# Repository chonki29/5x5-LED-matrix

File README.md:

# DIY 5x5 LED Matrix Digital Dice

A DIY 5x5 LED matrix made with 25 LEDs, an ESP32 and a zero PCB.

The matrix can display numbers 1–6 and works as a simple digital dice. Pressing the button generates a random number and shows a short rolling animation before displaying the result.

## Hardware

- ESP32
- 25 LEDs
- 5 × 330Ω resistors
- Push button
- Zero PCB

## Pinout

Rows:

- R1 → GPIO 22
- R2 → GPIO 19
- R3 → GPIO 23
- R4 → GPIO 18
- R5 → GPIO 5

Columns:

- C1 → GPIO 27
- C2 → GPIO 26
- C3 → GPIO 25
- C4 → GPIO 33
- C5 → GPIO 32

Button → GPIO 4

## Files

- `firmware/digital_dice.ino`    — ESP32 code
- `PCB/matrix display.kicad_sch` — KiCad schematic
- `PCB/matrix display.kicad_pro` — KiCad project
- `PCB/matrix display.kicad_pcb` — KiCad PCB layout
- `BOM.csv` — Bill of Materials

## Build

Designed in KiCad, soldered onto a zero PCB and programmed using Arduino IDE.

ChatGPT was used to assist with the C++ code 

thanks for checking out my project :)))

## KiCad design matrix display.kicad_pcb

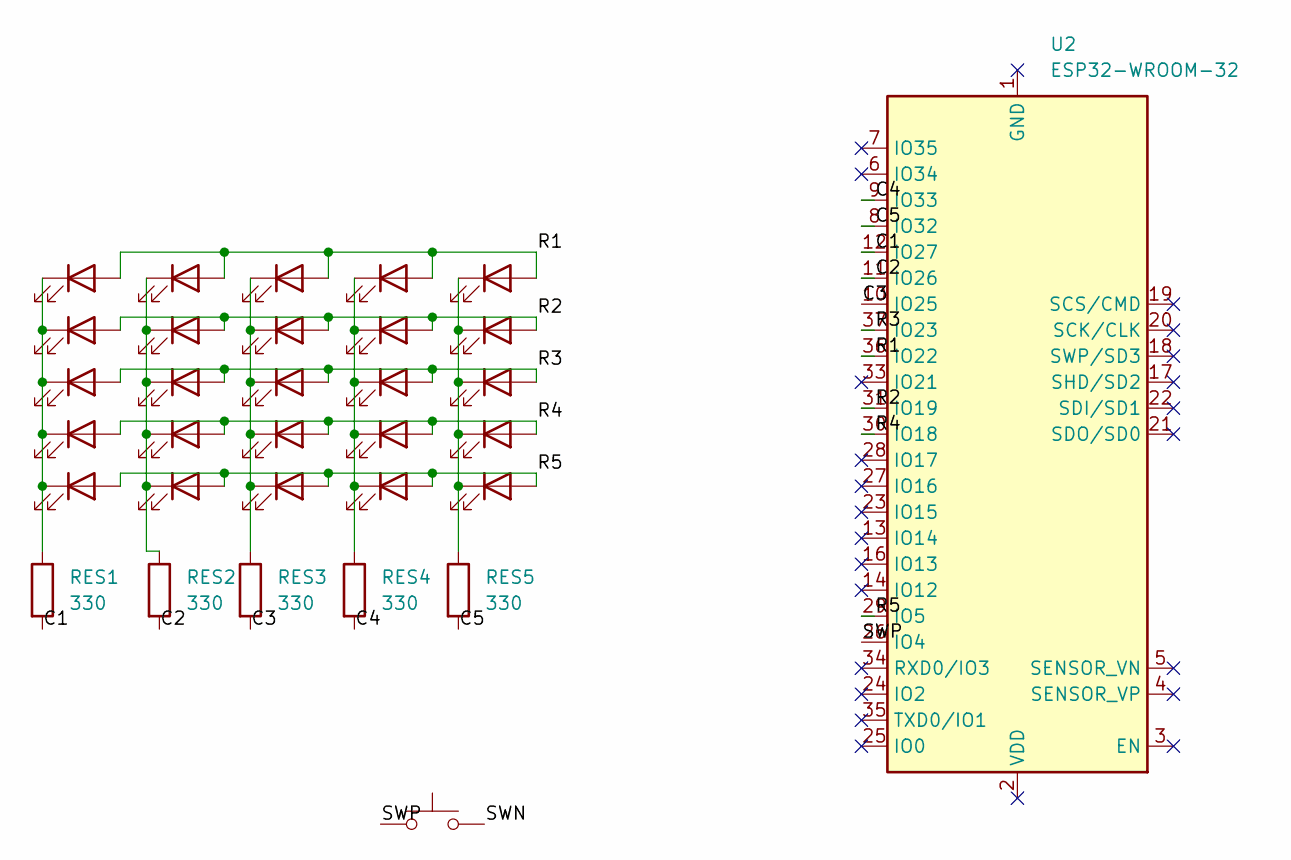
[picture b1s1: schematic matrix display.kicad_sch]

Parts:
D26, D27, D28, D29, D30, D31, D32, D33, D34, D35, D36, D37, D38, D39, D40, D41, D42, D43, D44, D45, D46, D47, D48, D49, D50: LED
RES1, RES2, RES3, RES4, RES5: 330
SW1: SW_Push
U2: ESP32-WROOM-32

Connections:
/C1: RES1.2, U2.12 (IO27); also elsewhere on the board
/C2: RES2.2, U2.11 (IO26); also elsewhere on the board
/C3: RES3.2, U2.10 (IO25); also elsewhere on the board
/C4: RES4.2, U2.9 (IO33); also elsewhere on the board
/C5: RES5.2, U2.8 (IO32); also elsewhere on the board
/R1: D26.2 (A), D31.2 (A), D36.2 (A), D41.2 (A), D46.2 (A), U2.36 (IO22); also elsewhere on the board
/R2: D27.2 (A), D32.2 (A), D37.2 (A), D42.2 (A), D47.2 (A), U2.31 (IO19); also elsewhere on the board
/R3: D28.2 (A), D33.2 (A), D38.2 (A), D43.2 (A), D48.2 (A), U2.37 (IO23); also elsewhere on the board
/R4: D29.2 (A), D34.2 (A), D39.2 (A), D44.2 (A), D49.2 (A), U2.30 (IO18); also elsewhere on the board
/R5: D30.2 (A), D35.2 (A), D40.2 (A), D45.2 (A), D50.2 (A), U2.29 (IO5); also elsewhere on the board
/SWN: SW1.2; also elsewhere on the board
/SWP: SW1.1, U2.26 (IO4); also elsewhere on the board
unnamed: D26.1 (K), D27.1 (K), D28.1 (K), D29.1 (K), D30.1 (K), RES1.1
unnamed: D31.1 (K), D32.1 (K), D33.1 (K), D34.1 (K), D35.1 (K), RES2.1
unnamed: D36.1 (K), D37.1 (K), D38.1 (K), D39.1 (K), D40.1 (K), RES3.1
unnamed: D41.1 (K), D42.1 (K), D43.1 (K), D44.1 (K), D45.1 (K), RES4.1
unnamed: D46.1 (K), D47.1 (K), D48.1 (K), D49.1 (K), D50.1 (K), RES5.1
unnamed: U2.1 (GND), U2.15 (GND), U2.38 (GND), U2.39 (GND)

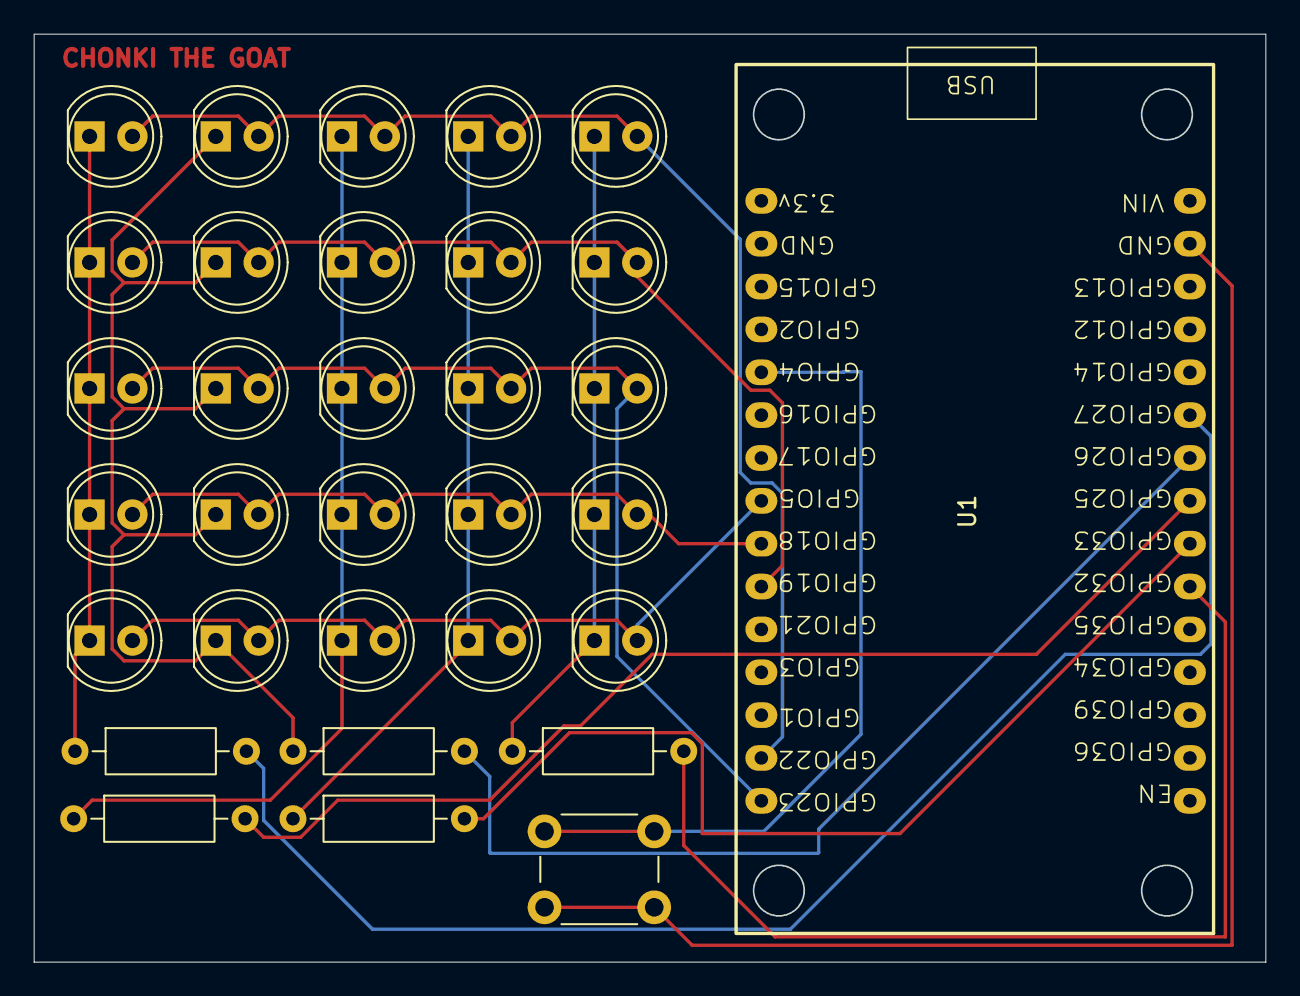
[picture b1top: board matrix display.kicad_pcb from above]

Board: 2 copper layers, 73.0 x 55.0 mm, 32 parts (0 on the bottom side), 17 nets.

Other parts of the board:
U1: ESP32_30pin

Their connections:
/C1: U1.6 (GPIO27); also elsewhere on the board
/C2: U1.7 (GPIO26); also elsewhere on the board
/C3: U1.8 (GPIO25); also elsewhere on the board
/C4: U1.9 (GPIO33); also elsewhere on the board
/C5: U1.10 (GPIO32); also elsewhere on the board
/R1: U1.29 (GPIO22); also elsewhere on the board
/R2: U1.25 (GPIO19); also elsewhere on the board
/R3: U1.30 (GPIO23); also elsewhere on the board
/R4: U1.24 (GPIO18); also elsewhere on the board
/R5: U1.23 (GPIO5); also elsewhere on the board
/SWN: U1.2 (GND); also elsewhere on the board
/SWP: U1.20 (GPIO4); also elsewhere on the board
